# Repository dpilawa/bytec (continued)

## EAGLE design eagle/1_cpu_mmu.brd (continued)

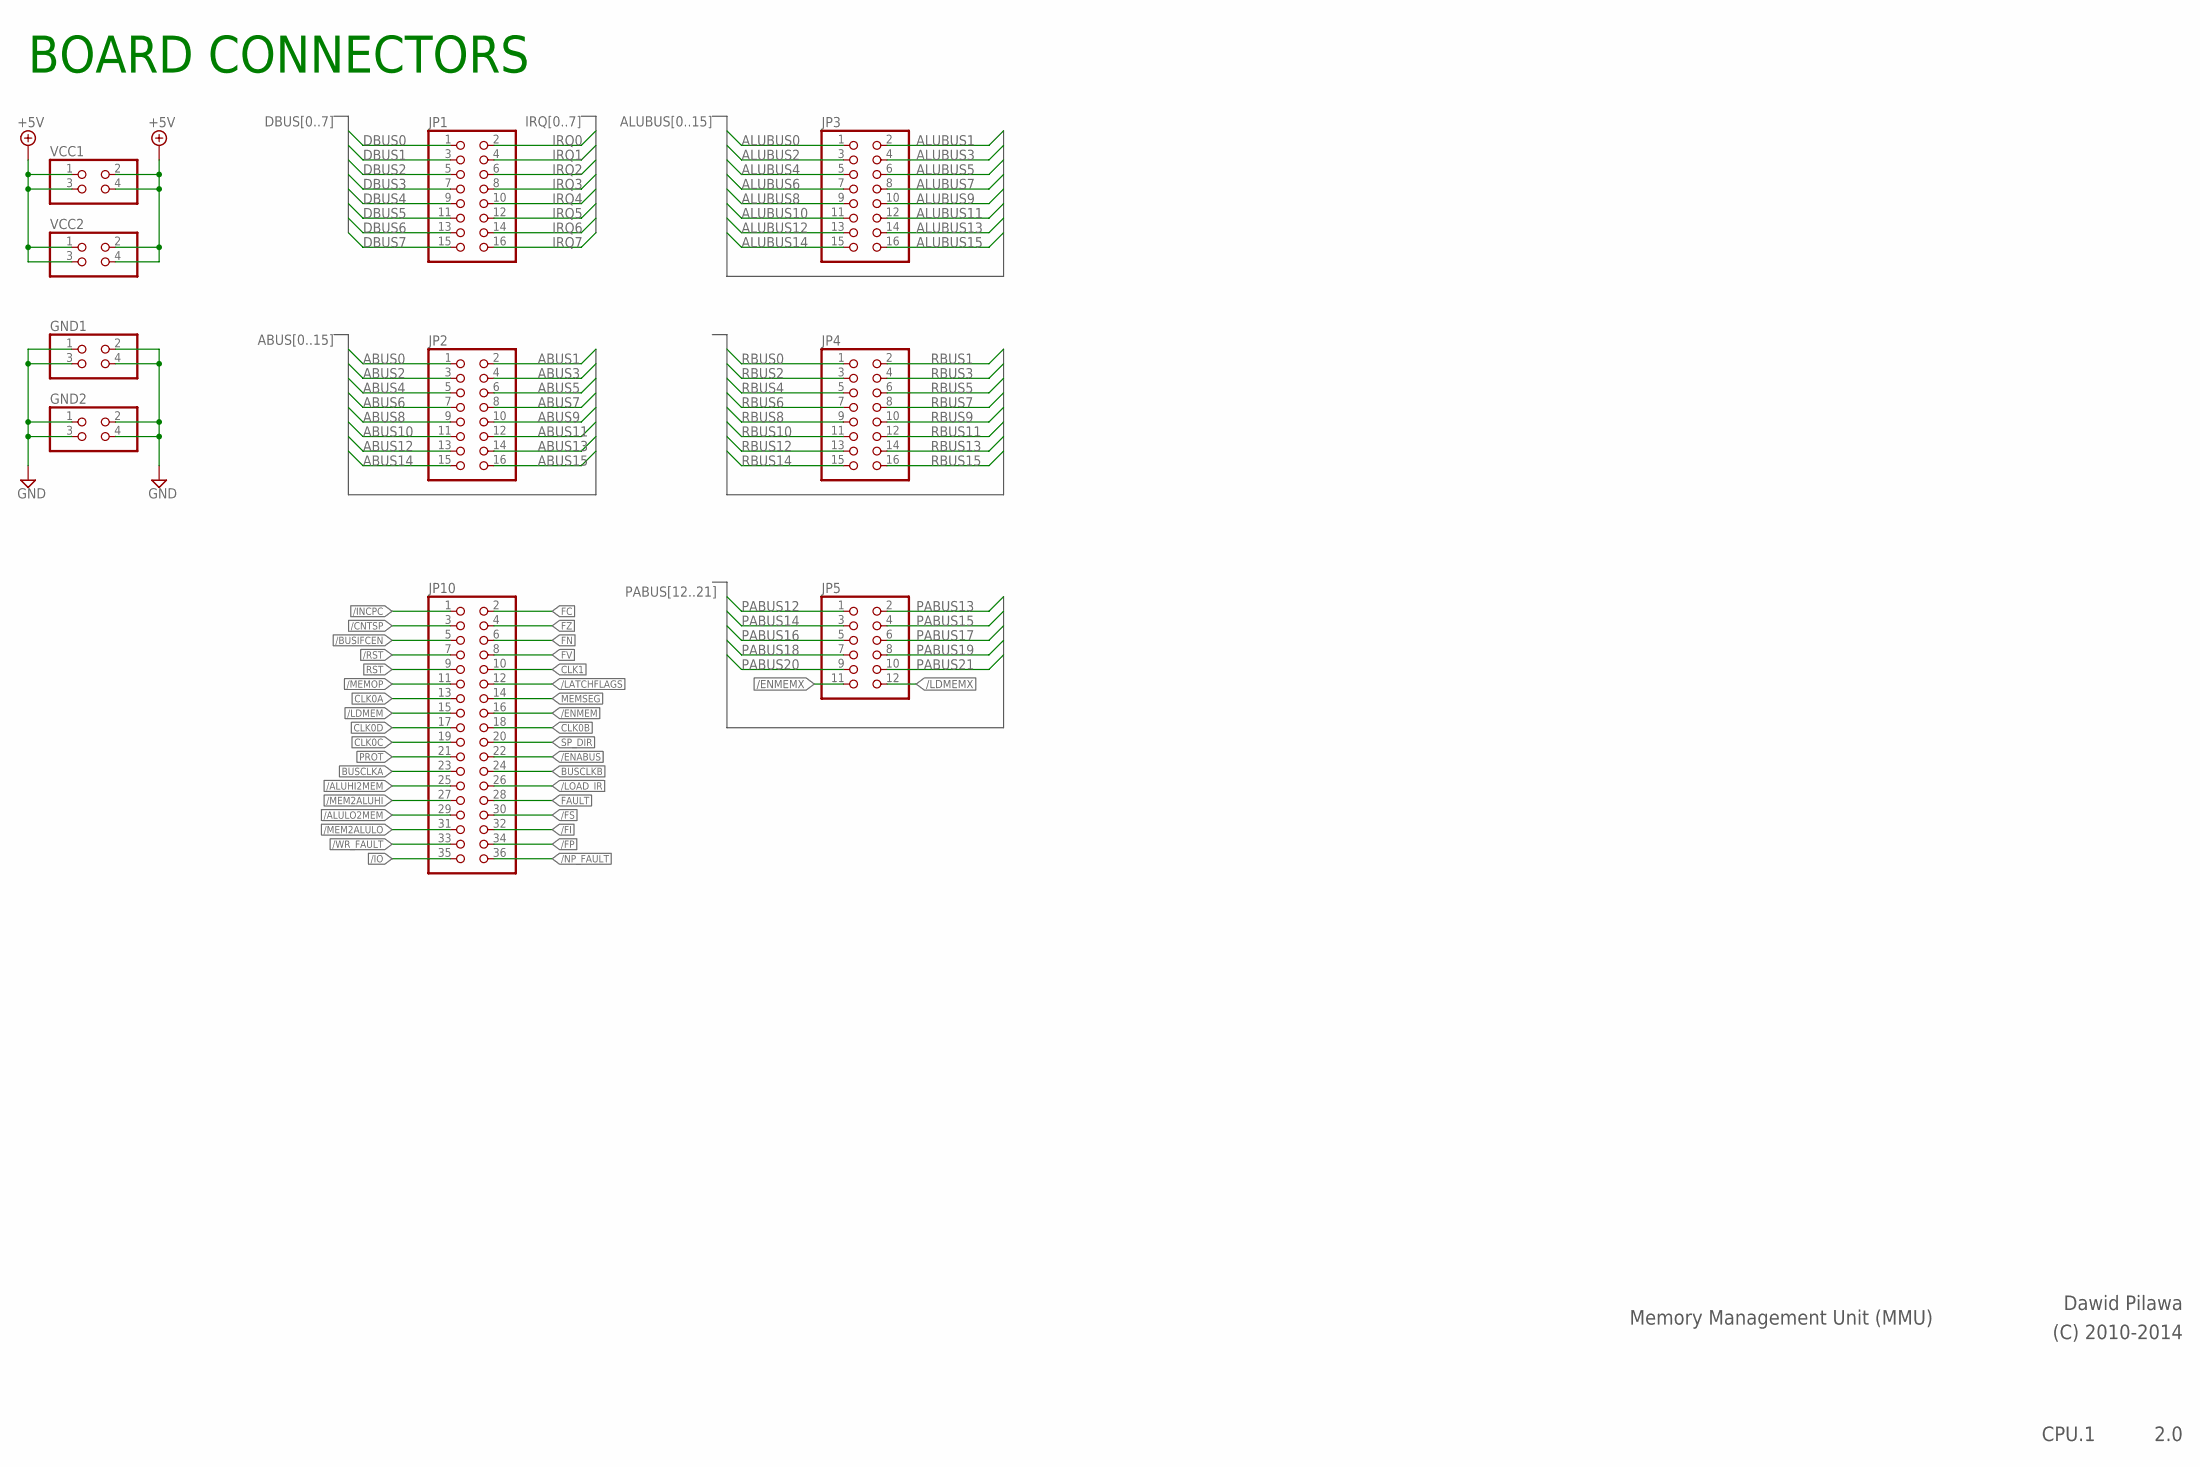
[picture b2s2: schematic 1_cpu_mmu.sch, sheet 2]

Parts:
GND1, GND2: PINHD-2X2; 2X02
JP1, JP2, JP3, JP4: PINHD-2X8; 2X08
JP5: PINHD-2X6; 2X06
JP10: PINHD-2X18; 2X18
VCC1, VCC2: PINHD-2X2; 2X02

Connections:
+5V: VCC1.1, VCC1.2, VCC1.3, VCC1.4, VCC2.1, VCC2.2, VCC2.3, VCC2.4; also elsewhere on the board
/ALUHI2MEM: JP10.25
/ALULO2MEM: JP10.29
/BUSIFCEN: JP10.5
/CNTSP: JP10.3
/ENABUS: JP10.22
/ENMEM: JP10.16; also elsewhere on the board
/ENMEMX: JP5.11; also elsewhere on the board
/FI: JP10.32
/FP: JP10.34; also elsewhere on the board
/FS: JP10.30; also elsewhere on the board
/INCPC: JP10.1
/IO: JP10.35; also elsewhere on the board
/LATCHFLAGS: JP10.12
/LDMEM: JP10.15; also elsewhere on the board
/LDMEMX: JP5.12; also elsewhere on the board
/LOAD_IR: JP10.26
/MEM2ALUHI: JP10.27
/MEM2ALULO: JP10.31
/MEMOP: JP10.11; also elsewhere on the board
/NP_FAULT: JP10.36; also elsewhere on the board
/RST: JP10.7
/WR_FAULT: JP10.33; also elsewhere on the board
ABUS0: JP2.1; also elsewhere on the board
ABUS1: JP2.2; also elsewhere on the board
ABUS2: JP2.3; also elsewhere on the board
ABUS3: JP2.4; also elsewhere on the board
ABUS4: JP2.5; also elsewhere on the board
ABUS5: JP2.6; also elsewhere on the board
ABUS6: JP2.7; also elsewhere on the board
ABUS7: JP2.8; also elsewhere on the board
ABUS8: JP2.9; also elsewhere on the board
ABUS9: JP2.10; also elsewhere on the board
ABUS10: JP2.11; also elsewhere on the board
ABUS11: JP2.12; also elsewhere on the board
ABUS12: JP2.13; also elsewhere on the board
ABUS13: JP2.14; also elsewhere on the board
ABUS14: JP2.15; also elsewhere on the board
ABUS15: JP2.16; also elsewhere on the board
ALUBUS0: JP3.1
ALUBUS1: JP3.2
ALUBUS2: JP3.3
ALUBUS3: JP3.4
ALUBUS4: JP3.5
ALUBUS5: JP3.6
ALUBUS6: JP3.7
ALUBUS7: JP3.8
ALUBUS8: JP3.9
ALUBUS9: JP3.10
ALUBUS10: JP3.11
ALUBUS11: JP3.12
ALUBUS12: JP3.13
ALUBUS13: JP3.14
ALUBUS14: JP3.15
ALUBUS15: JP3.16
BUSCLKA: JP10.23; also elsewhere on the board
BUSCLKB: JP10.24
CLK0A: JP10.13
CLK0B: JP10.18
CLK0C: JP10.19
CLK0D: JP10.17
CLK1: JP10.10
DBUS0: JP1.1; also elsewhere on the board
DBUS1: JP1.3; also elsewhere on the board
DBUS2: JP1.5; also elsewhere on the board
DBUS3: JP1.7; also elsewhere on the board
DBUS4: JP1.9; also elsewhere on the board
DBUS5: JP1.11; also elsewhere on the board
DBUS6: JP1.13; also elsewhere on the board
DBUS7: JP1.15; also elsewhere on the board
FAULT: JP10.28; also elsewhere on the board
FC: JP10.2
FN: JP10.6
FV: JP10.8
FZ: JP10.4
GND: GND1.1, GND1.2, GND1.3, GND1.4, GND2.1, GND2.2, GND2.3, GND2.4; also elsewhere on the board
IRQ0: JP1.2
IRQ1: JP1.4
IRQ2: JP1.6
IRQ3: JP1.8
IRQ4: JP1.10
IRQ5: JP1.12
IRQ6: JP1.14
IRQ7: JP1.16
MEMSEG: JP10.14; also elsewhere on the board
PABUS12: JP5.1; also elsewhere on the board
PABUS13: JP5.2; also elsewhere on the board
PABUS14: JP5.3; also elsewhere on the board
PABUS15: JP5.4; also elsewhere on the board
PABUS16: JP5.5; also elsewhere on the board
PABUS17: JP5.6; also elsewhere on the board
PABUS18: JP5.7; also elsewhere on the board
PABUS19: JP5.8; also elsewhere on the board
PABUS20: JP5.9; also elsewhere on the board
PABUS21: JP5.10; also elsewhere on the board
PROT: JP10.21
RBUS0: JP4.1
RBUS1: JP4.2
RBUS2: JP4.3
RBUS3: JP4.4
RBUS4: JP4.5
RBUS5: JP4.6
RBUS6: JP4.7
RBUS7: JP4.8
RBUS8: JP4.9
RBUS9: JP4.10
RBUS10: JP4.11
RBUS11: JP4.12
RBUS12: JP4.13
RBUS13: JP4.14
RBUS14: JP4.15
RBUS15: JP4.16
RST: JP10.9
SP_DIR: JP10.20

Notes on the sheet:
Memory Management Unit (MMU)
Dawid Pilawa
(C) 2010-2014
CPU.1
2.0
BOARD CONNECTORS

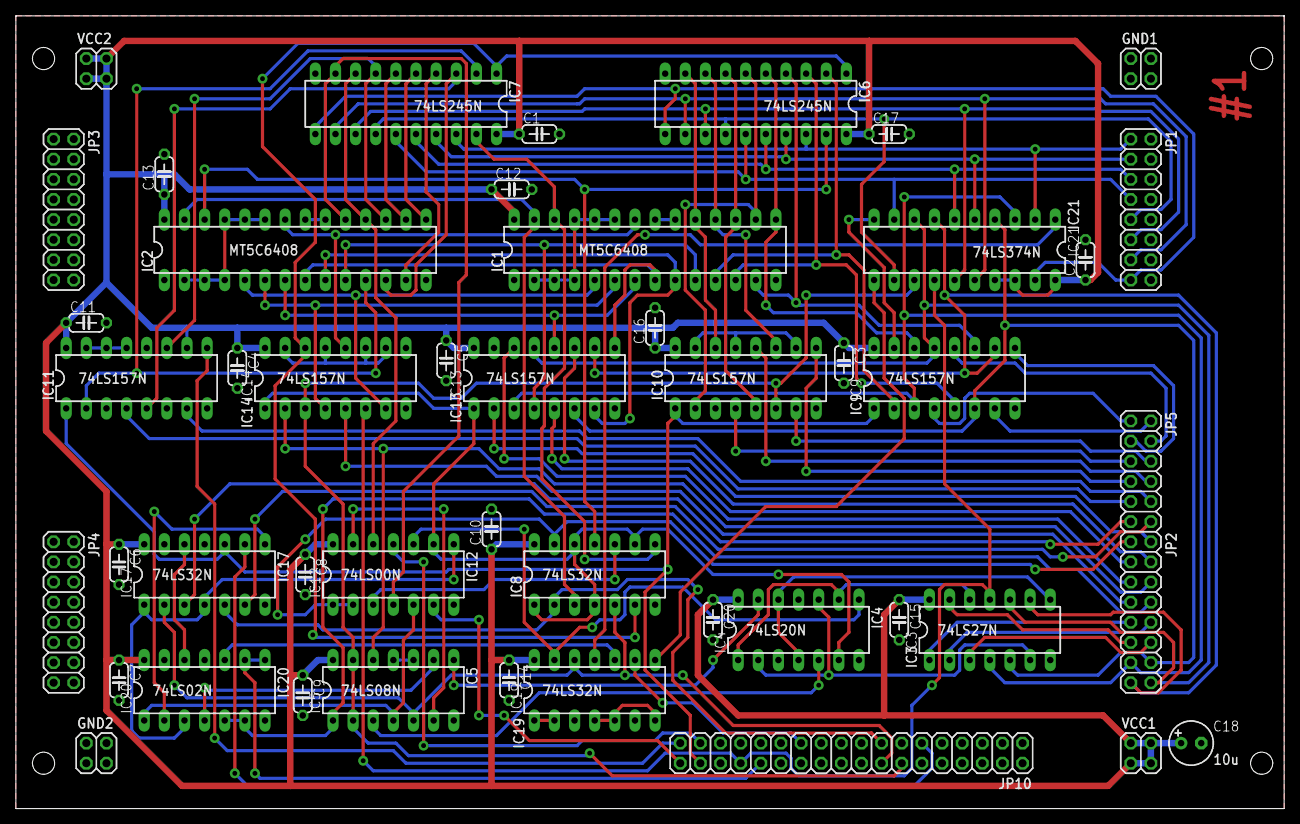
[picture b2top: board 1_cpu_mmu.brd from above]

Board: 2 copper layers, 160.0 x 100.0 mm, 47 parts (0 on the bottom side), 93 nets.

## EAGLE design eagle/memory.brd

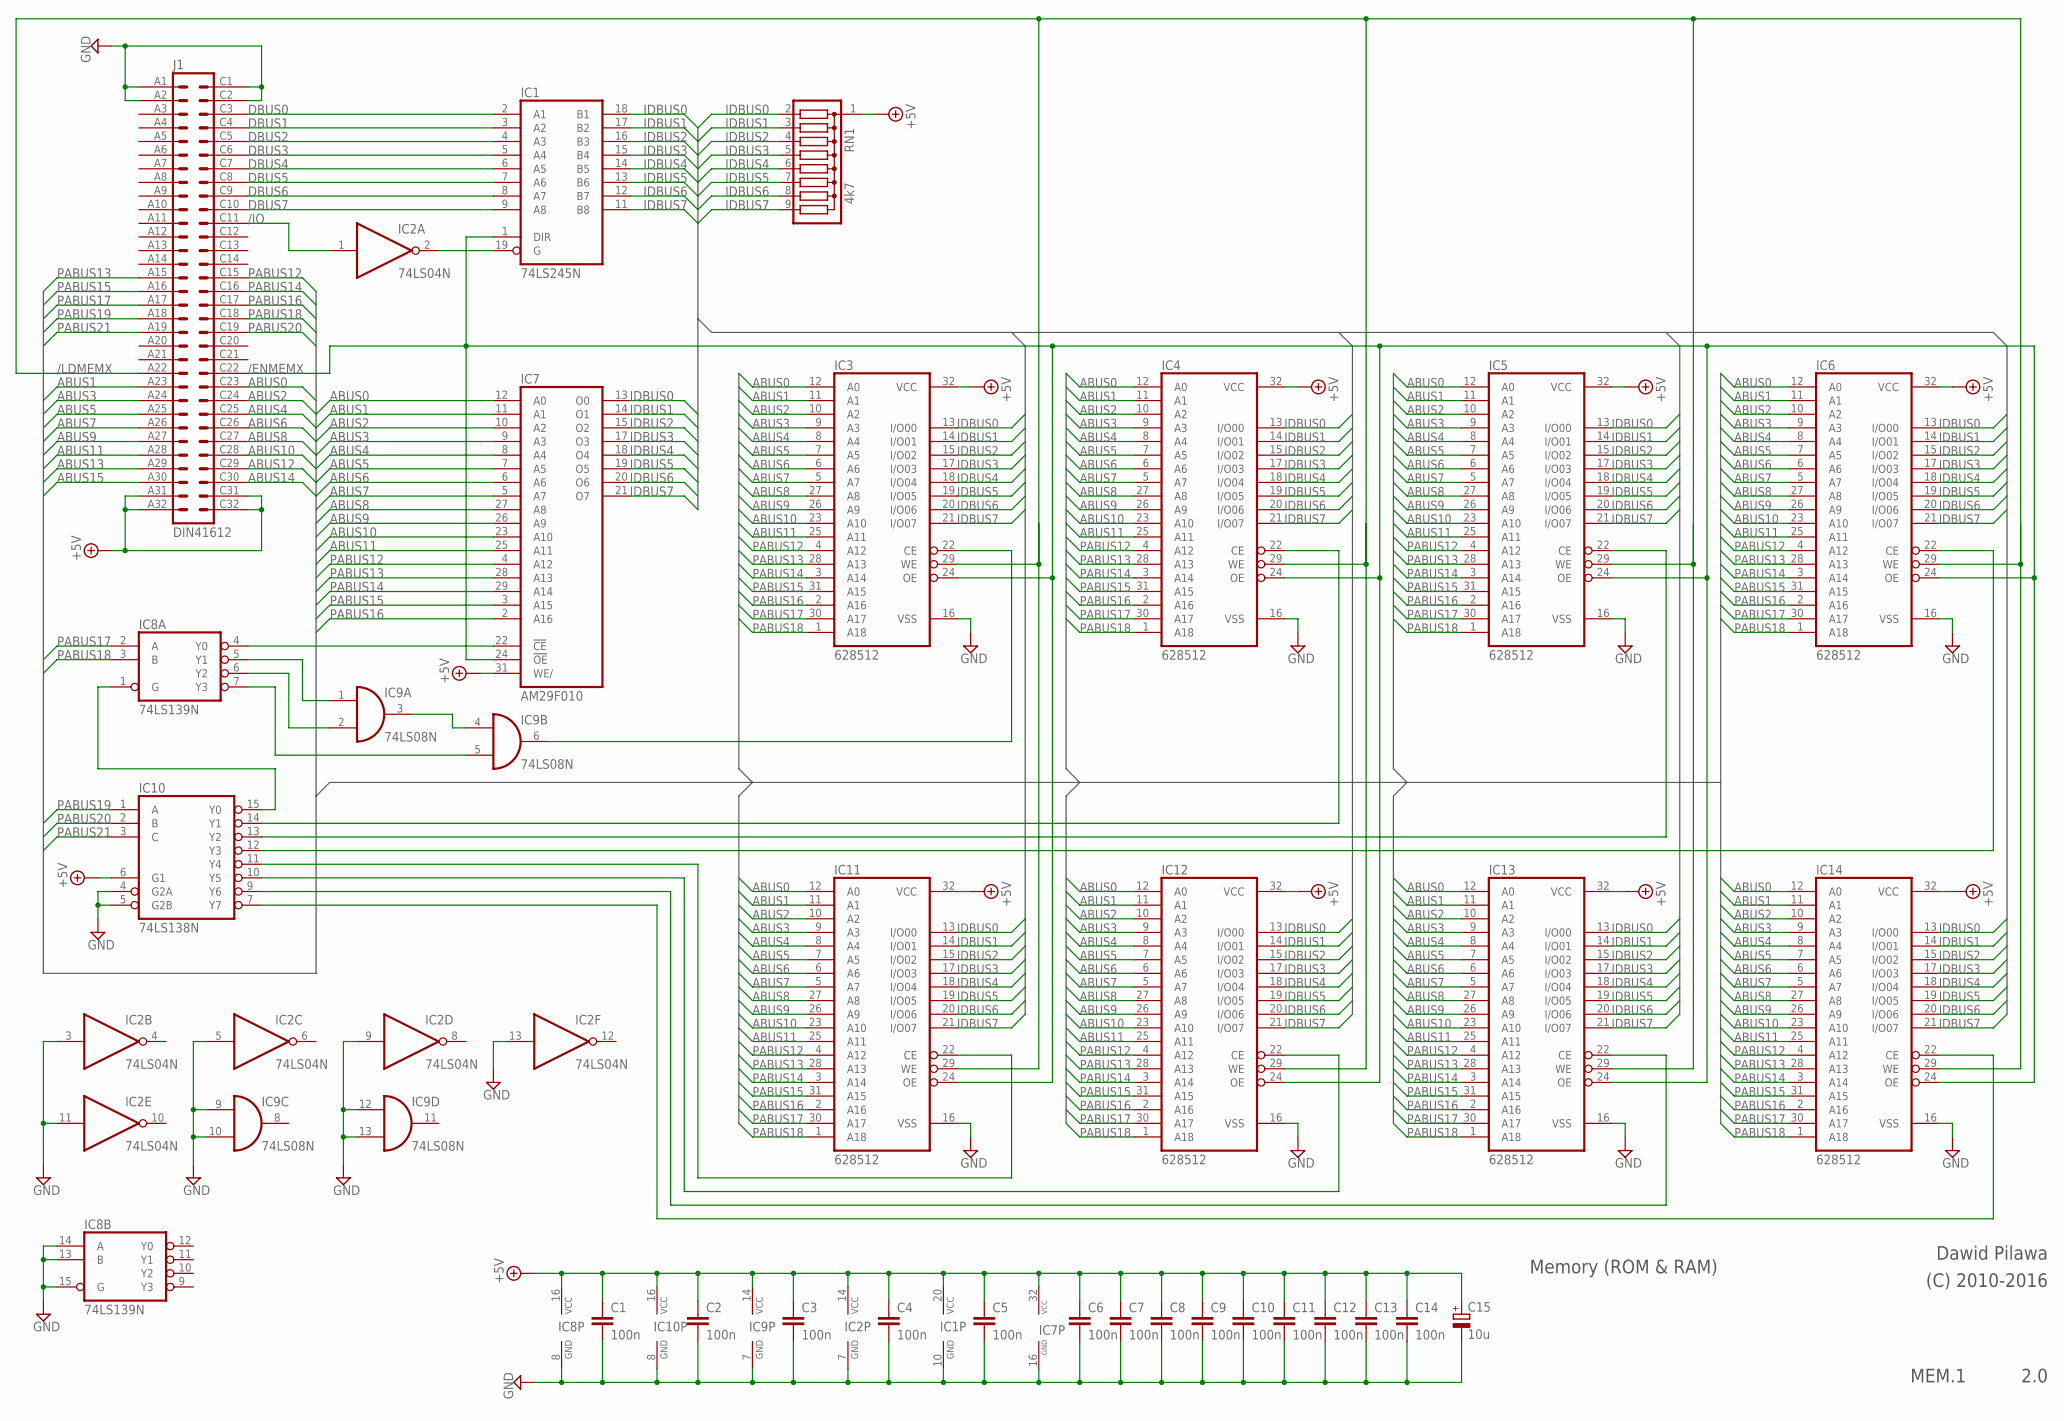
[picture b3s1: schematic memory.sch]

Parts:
C1, C2, C3, C4, C5, C6, C7, C8, C9, C10, C11, C12, C13, C14: 100n; C050-024X044
C15: 10u; E2,5-6
IC1: 74LS245N; DIL20
IC2: 74LS04N; DIL14
IC3, IC4, IC5, IC6, IC11, IC12, IC13, IC14: 628512; DIL32
IC7: AM29F010; DIL32-6
IC8: 74LS139N; DIL16
IC9: 74LS08N; DIL14
IC10: 74LS138N; DIL16
J1: DIN41612; VG64B
RN1: 4k7; SIL9

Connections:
+5V: C1.1, C2.1, C3.1, C4.1, C5.1, C6.1, C7.1, C8.1, C9.1, C10.1, C11.1, C12.1, C13.1, C14.1, C15.+, IC1.20 (VCC), IC2.14 (VCC), IC3.32 (VCC), IC4.32 (VCC), IC5.32 (VCC), IC6.32 (VCC), IC7.31 (WE/), IC7.32 (VCC), IC8.16 (VCC), IC9.14 (VCC), IC10.6 (G1), IC10.16 (VCC), IC11.32 (VCC), IC12.32 (VCC), IC13.32 (VCC), IC14.32 (VCC), J1.A31, J1.A32, J1.C31, J1.C32, RN1.1
/BANK0RAM: IC3.22 (CE), IC9.6 (O)
/BANK1: IC4.22 (CE), IC10.14 (Y1)
/BANK2: IC5.22 (CE), IC10.13 (Y2)
/BANK3: IC6.22 (CE), IC10.12 (Y3)
/BANK4: IC10.11 (Y4), IC11.22 (CE)
/BANK5: IC10.10 (Y5), IC12.22 (CE)
/BANK6: IC10.9 (Y6), IC13.22 (CE)
/BANK7: IC10.7 (Y7), IC14.22 (CE)
/ENMEMX: IC1.1 (DIR), IC3.24 (OE), IC4.24 (OE), IC5.24 (OE), IC6.24 (OE), IC7.24 (!OE), IC11.24 (OE), IC12.24 (OE), IC13.24 (OE), IC14.24 (OE), J1.C22
/IO: IC2.1 (I), J1.C11
/LDMEMX: IC3.29 (WE), IC4.29 (WE), IC5.29 (WE), IC6.29 (WE), IC11.29 (WE), IC12.29 (WE), IC13.29 (WE), IC14.29 (WE), J1.A22
ABUS0: IC3.12 (A0), IC4.12 (A0), IC5.12 (A0), IC6.12 (A0), IC7.12 (A0), IC11.12 (A0), IC12.12 (A0), IC13.12 (A0), IC14.12 (A0), J1.C23
ABUS1: IC3.11 (A1), IC4.11 (A1), IC5.11 (A1), IC6.11 (A1), IC7.11 (A1), IC11.11 (A1), IC12.11 (A1), IC13.11 (A1), IC14.11 (A1), J1.A23
ABUS2: IC3.10 (A2), IC4.10 (A2), IC5.10 (A2), IC6.10 (A2), IC7.10 (A2), IC11.10 (A2), IC12.10 (A2), IC13.10 (A2), IC14.10 (A2), J1.C24
ABUS3: IC3.9 (A3), IC4.9 (A3), IC5.9 (A3), IC6.9 (A3), IC7.9 (A3), IC11.9 (A3), IC12.9 (A3), IC13.9 (A3), IC14.9 (A3), J1.A24
ABUS4: IC3.8 (A4), IC4.8 (A4), IC5.8 (A4), IC6.8 (A4), IC7.8 (A4), IC11.8 (A4), IC12.8 (A4), IC13.8 (A4), IC14.8 (A4), J1.C25
ABUS5: IC3.7 (A5), IC4.7 (A5), IC5.7 (A5), IC6.7 (A5), IC7.7 (A5), IC11.7 (A5), IC12.7 (A5), IC13.7 (A5), IC14.7 (A5), J1.A25
ABUS6: IC3.6 (A6), IC4.6 (A6), IC5.6 (A6), IC6.6 (A6), IC7.6 (A6), IC11.6 (A6), IC12.6 (A6), IC13.6 (A6), IC14.6 (A6), J1.C26
ABUS7: IC3.5 (A7), IC4.5 (A7), IC5.5 (A7), IC6.5 (A7), IC7.5 (A7), IC11.5 (A7), IC12.5 (A7), IC13.5 (A7), IC14.5 (A7), J1.A26
ABUS8: IC3.27 (A8), IC4.27 (A8), IC5.27 (A8), IC6.27 (A8), IC7.27 (A8), IC11.27 (A8), IC12.27 (A8), IC13.27 (A8), IC14.27 (A8), J1.C27
ABUS9: IC3.26 (A9), IC4.26 (A9), IC5.26 (A9), IC6.26 (A9), IC7.26 (A9), IC11.26 (A9), IC12.26 (A9), IC13.26 (A9), IC14.26 (A9), J1.A27
ABUS10: IC3.23 (A10), IC4.23 (A10), IC5.23 (A10), IC6.23 (A10), IC7.23 (A10), IC11.23 (A10), IC12.23 (A10), IC13.23 (A10), IC14.23 (A10), J1.C28
ABUS11: IC3.25 (A11), IC4.25 (A11), IC5.25 (A11), IC6.25 (A11), IC7.25 (A11), IC11.25 (A11), IC12.25 (A11), IC13.25 (A11), IC14.25 (A11), J1.A28
ABUS12: J1.C29
ABUS13: J1.A29
ABUS14: J1.C30
ABUS15: J1.A30
DBUS0: IC1.2 (A1), J1.C3
DBUS1: IC1.3 (A2), J1.C4
DBUS2: IC1.4 (A3), J1.C5
DBUS3: IC1.5 (A4), J1.C6
DBUS4: IC1.6 (A5), J1.C7
DBUS5: IC1.7 (A6), J1.C8
DBUS6: IC1.8 (A7), J1.C9
DBUS7: IC1.9 (A8), J1.C10
GND: C1.2, C2.2, C3.2, C4.2, C5.2, C6.2, C7.2, C8.2, C9.2, C10.2, C11.2, C12.2, C13.2, C14.2, C15.-, IC1.10 (GND), IC2.3 (I), IC2.5 (I), IC2.7 (GND), IC2.9 (I), IC2.11 (I), IC2.13 (I), IC3.16 (VSS), IC4.16 (VSS), IC5.16 (VSS), IC6.16 (VSS), IC7.16 (GND), IC8.8 (GND), IC8.13 (B), IC8.14 (A), IC8.15 (G), IC9.7 (GND), IC9.9 (I0), IC9.10 (I1), IC9.12 (I0), IC9.13 (I1), IC10.4 (G2A), IC10.5 (G2B), IC10.8 (GND), IC11.16 (VSS), IC12.16 (VSS), IC13.16 (VSS), IC14.16 (VSS), J1.A1, J1.A2, J1.C1, J1.C2
IDBUS0: IC1.18 (B1), IC3.13 (I/O00), IC4.13 (I/O00), IC5.13 (I/O00), IC6.13 (I/O00), IC7.13 (O0), IC11.13 (I/O00), IC12.13 (I/O00), IC13.13 (I/O00), IC14.13 (I/O00), RN1.2
IDBUS1: IC1.17 (B2), IC3.14 (I/O01), IC4.14 (I/O01), IC5.14 (I/O01), IC6.14 (I/O01), IC7.14 (O1), IC11.14 (I/O01), IC12.14 (I/O01), IC13.14 (I/O01), IC14.14 (I/O01), RN1.3
IDBUS2: IC1.16 (B3), IC3.15 (I/O02), IC4.15 (I/O02), IC5.15 (I/O02), IC6.15 (I/O02), IC7.15 (O2), IC11.15 (I/O02), IC12.15 (I/O02), IC13.15 (I/O02), IC14.15 (I/O02), RN1.4
IDBUS3: IC1.15 (B4), IC3.17 (I/O03), IC4.17 (I/O03), IC5.17 (I/O03), IC6.17 (I/O03), IC7.17 (O3), IC11.17 (I/O03), IC12.17 (I/O03), IC13.17 (I/O03), IC14.17 (I/O03), RN1.5
IDBUS4: IC1.14 (B5), IC3.18 (I/O04), IC4.18 (I/O04), IC5.18 (I/O04), IC6.18 (I/O04), IC7.18 (O4), IC11.18 (I/O04), IC12.18 (I/O04), IC13.18 (I/O04), IC14.18 (I/O04), RN1.6
IDBUS5: IC1.13 (B6), IC3.19 (I/O05), IC4.19 (I/O05), IC5.19 (I/O05), IC6.19 (I/O05), IC7.19 (O5), IC11.19 (I/O05), IC12.19 (I/O05), IC13.19 (I/O05), IC14.19 (I/O05), RN1.7
IDBUS6: IC1.12 (B7), IC3.20 (I/O06), IC4.20 (I/O06), IC5.20 (I/O06), IC6.20 (I/O06), IC7.20 (O6), IC11.20 (I/O06), IC12.20 (I/O06), IC13.20 (I/O06), IC14.20 (I/O06), RN1.8
IDBUS7: IC1.11 (B8), IC3.21 (I/O07), IC4.21 (I/O07), IC5.21 (I/O07), IC6.21 (I/O07), IC7.21 (O7), IC11.21 (I/O07), IC12.21 (I/O07), IC13.21 (I/O07), IC14.21 (I/O07), RN1.9
unnamed: IC1.19 (G), IC2.2 (O)
unnamed: IC8.1 (G), IC10.15 (Y0)
unnamed: IC8.5 (Y1), IC9.1 (I0)
unnamed: IC8.6 (Y2), IC9.2 (I1)
unnamed: IC7.22 (!CE), IC8.4 (Y0)
unnamed: IC8.7 (Y3), IC9.5 (I1)
unnamed: IC9.3 (O), IC9.4 (I0)
PABUS12: IC3.4 (A12), IC4.4 (A12), IC5.4 (A12), IC6.4 (A12), IC7.4 (A12), IC11.4 (A12), IC12.4 (A12), IC13.4 (A12), IC14.4 (A12), J1.C15
PABUS13: IC3.28 (A13), IC4.28 (A13), IC5.28 (A13), IC6.28 (A13), IC7.28 (A13), IC11.28 (A13), IC12.28 (A13), IC13.28 (A13), IC14.28 (A13), J1.A15
PABUS14: IC3.3 (A14), IC4.3 (A14), IC5.3 (A14), IC6.3 (A14), IC7.29 (A14), IC11.3 (A14), IC12.3 (A14), IC13.3 (A14), IC14.3 (A14), J1.C16
PABUS15: IC3.31 (A15), IC4.31 (A15), IC5.31 (A15), IC6.31 (A15), IC7.3 (A15), IC11.31 (A15), IC12.31 (A15), IC13.31 (A15), IC14.31 (A15), J1.A16
PABUS16: IC3.2 (A16), IC4.2 (A16), IC5.2 (A16), IC6.2 (A16), IC7.2 (A16), IC11.2 (A16), IC12.2 (A16), IC13.2 (A16), IC14.2 (A16), J1.C17
PABUS17: IC3.30 (A17), IC4.30 (A17), IC5.30 (A17), IC6.30 (A17), IC8.2 (A), IC11.30 (A17), IC12.30 (A17), IC13.30 (A17), IC14.30 (A17), J1.A17
PABUS18: IC3.1 (A18), IC4.1 (A18), IC5.1 (A18), IC6.1 (A18), IC8.3 (B), IC11.1 (A18), IC12.1 (A18), IC13.1 (A18), IC14.1 (A18), J1.C18
PABUS19: IC10.1 (A), J1.A18
PABUS20: IC10.2 (B), J1.C19
PABUS21: IC10.3 (C), J1.A19

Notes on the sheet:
Memory (ROM & RAM)
Dawid Pilawa
(C) 2010-2016
MEM.1
2.0

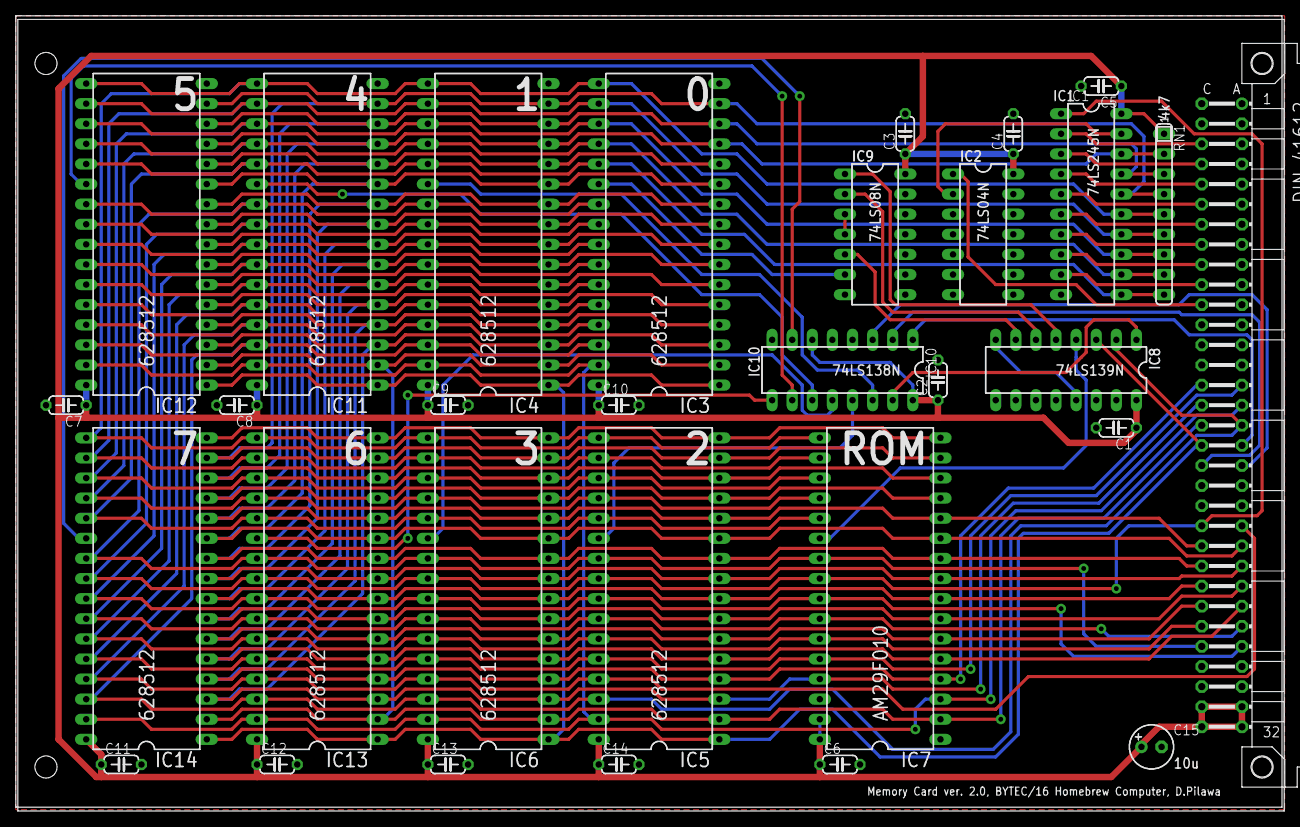
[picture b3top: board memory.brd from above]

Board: 2 copper layers, 160.0 x 100.0 mm, 31 parts (0 on the bottom side), 58 nets.

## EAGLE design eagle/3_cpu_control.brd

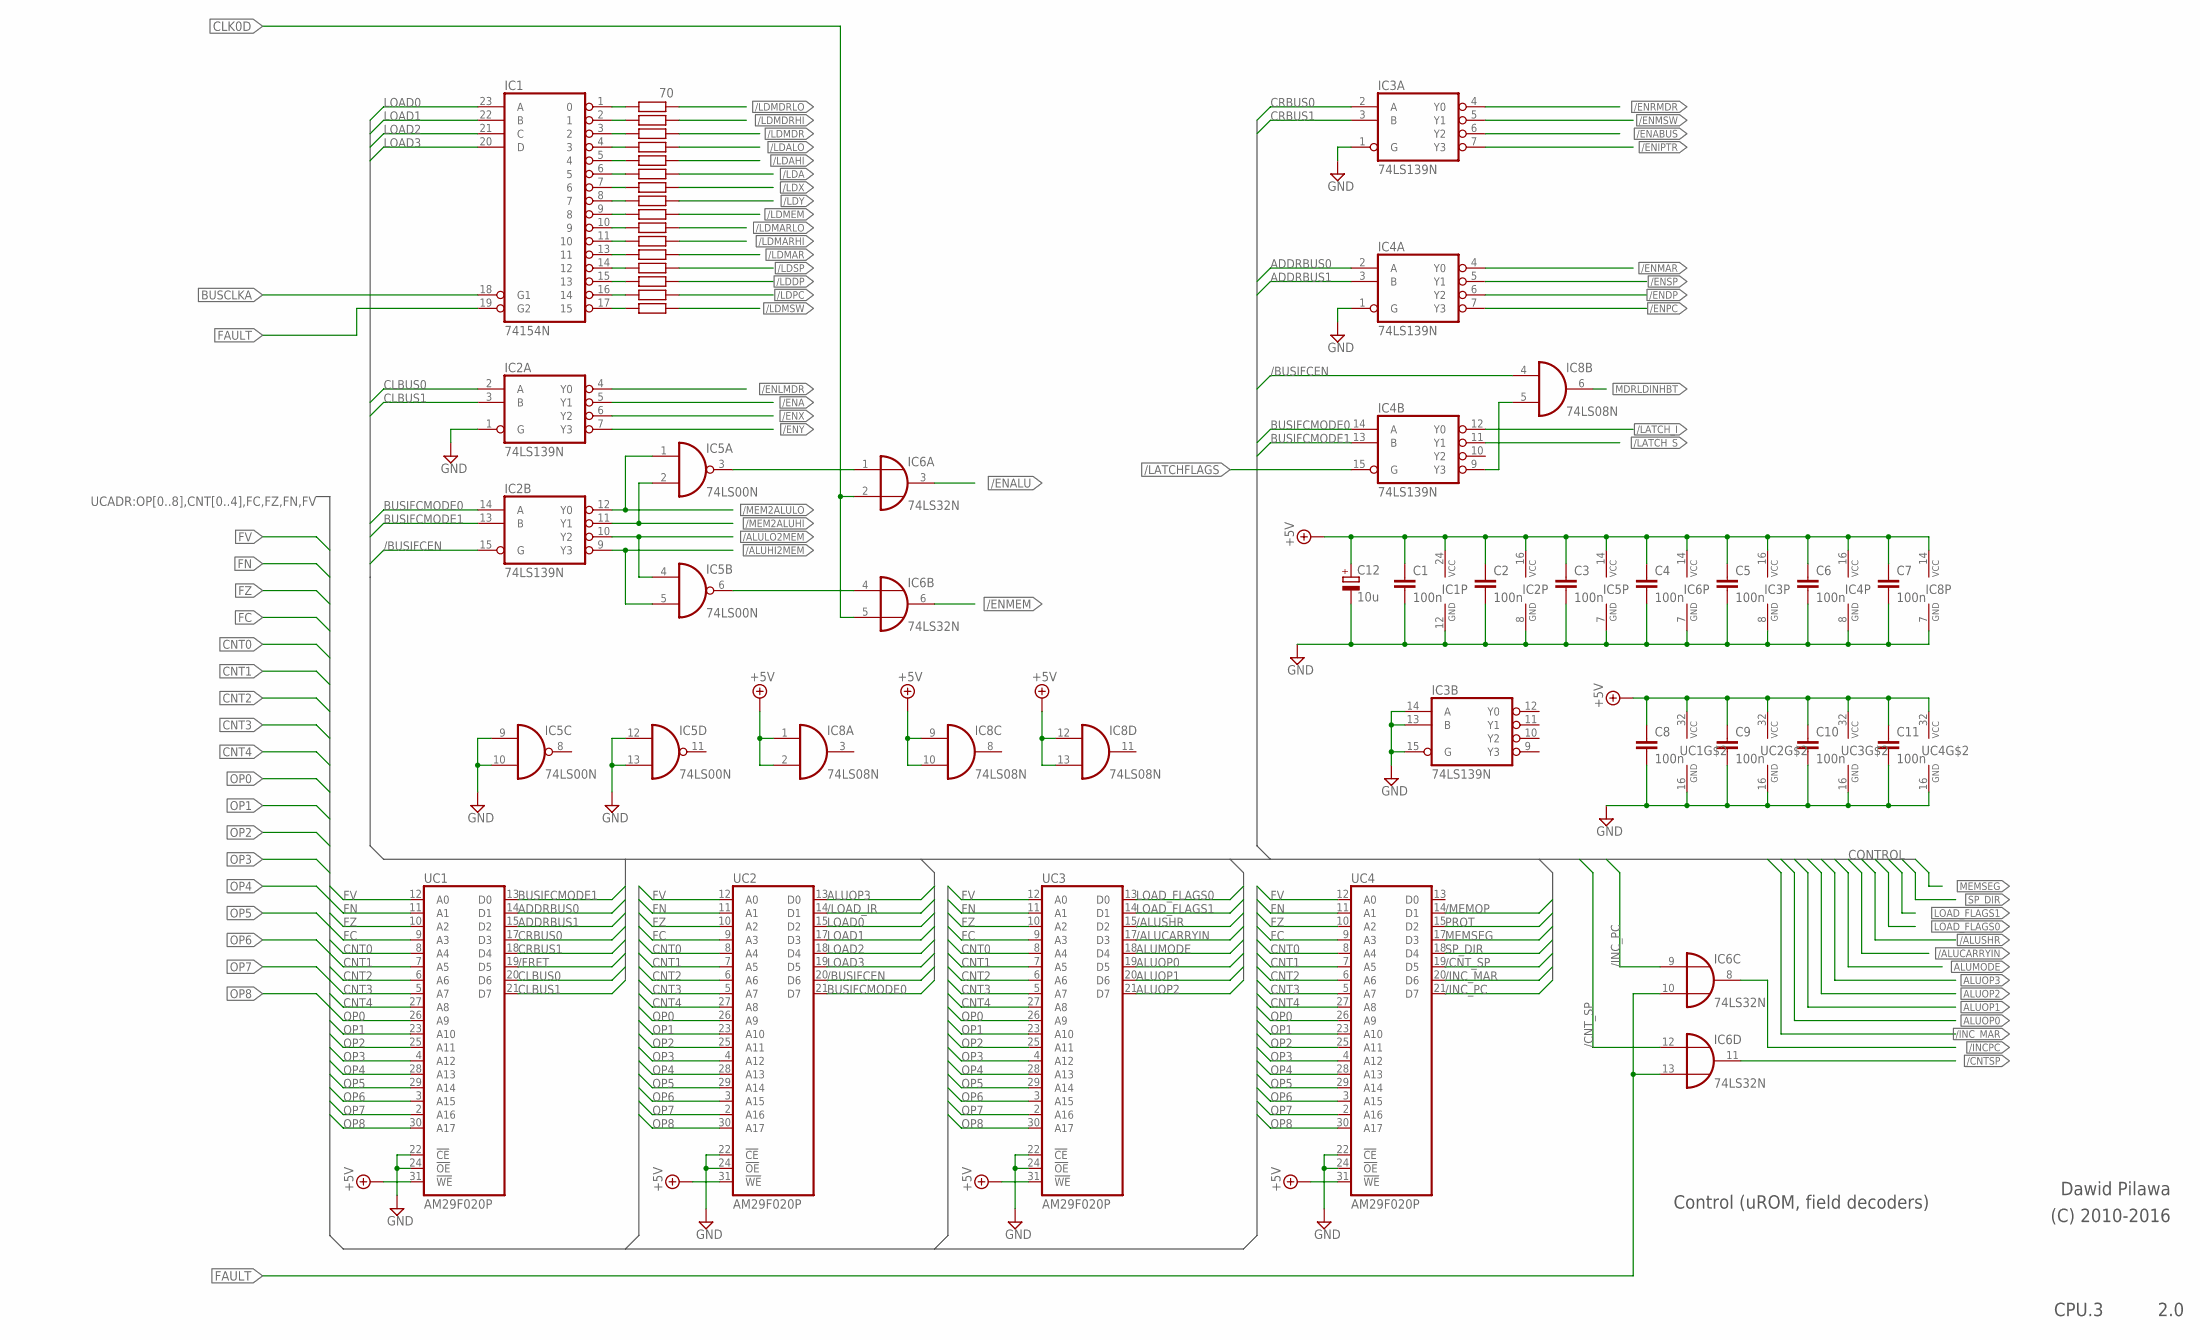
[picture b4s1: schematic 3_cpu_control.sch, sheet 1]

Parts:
C1, C2, C3, C4, C5, C6, C7, C8, C9, C10, C11: 100n; C050-024X044
C12: 10u; E5-6
IC1: 74154N; DIL24-6
IC2, IC3, IC4: 74LS139N; DIL16
IC5: 74LS00N; DIL14
IC6: 74LS32N; DIL14
IC8: 74LS08N; DIL14
R1: 70; 0204/7
R2, R3, R4, R5, R6, R7, R8, R9, R10, R11, R12, R13, R14, R15, R16: R-EU_0204/7; 0204/7
UC1, UC2, UC3, UC4: AM29F020P; DIL32-6

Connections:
+5V: C1.1, C2.1, C3.1, C4.1, C5.1, C6.1, C7.1, C8.1, C9.1, C10.1, C11.1, C12.+, IC1.24 (VCC), IC2.16 (VCC), IC3.16 (VCC), IC4.16 (VCC), IC5.14 (VCC), IC6.14 (VCC), IC8.1 (I0), IC8.2 (I1), IC8.9 (I0), IC8.10 (I1), IC8.12 (I0), IC8.13 (I1), IC8.14 (VCC), UC1.31 (!WE), UC1.32 (AVCC), UC2.31 (!WE), UC2.32 (AVCC), UC3.31 (!WE), UC3.32 (AVCC), UC4.31 (!WE), UC4.32 (AVCC); also elsewhere on the board
/ALUCARRYIN: UC3.17 (D3); also elsewhere on the board
/ALUHI2MEM: IC2.9 (Y3), IC5.5 (I1); also elsewhere on the board
/ALULO2MEM: IC2.10 (Y2), IC5.4 (I0); also elsewhere on the board
/ALUSHR: UC3.15 (D2); also elsewhere on the board
/BUSIFCEN: IC2.15 (G), IC8.4 (I0), UC2.20 (D6); also elsewhere on the board
/CNTSP: IC6.11 (O); also elsewhere on the board
/CNT_SP: IC6.12 (I0), UC4.19 (D5)
/ENA: IC2.5 (Y1); also elsewhere on the board
/ENABUS: IC3.6 (Y2); also elsewhere on the board
/ENALU: IC6.3 (O); also elsewhere on the board
/ENDP: IC4.6 (Y2); also elsewhere on the board
/ENIPTR: IC3.7 (Y3); also elsewhere on the board
/ENLMDR: IC2.4 (Y0); also elsewhere on the board
/ENMAR: IC4.4 (Y0); also elsewhere on the board
/ENMEM: IC6.6 (O); also elsewhere on the board
/ENMSW: IC3.5 (Y1); also elsewhere on the board
/ENPC: IC4.7 (Y3); also elsewhere on the board
/ENRMDR: IC3.4 (Y0); also elsewhere on the board
/ENSP: IC4.5 (Y1); also elsewhere on the board
/ENX: IC2.6 (Y2); also elsewhere on the board
/ENY: IC2.7 (Y3); also elsewhere on the board
/FRET: UC1.19 (D5); also elsewhere on the board
/INCPC: IC6.8 (O); also elsewhere on the board
/INC_MAR: UC4.20 (D6); also elsewhere on the board
/INC_PC: IC6.9 (I0), UC4.21 (D7)
/LATCHFLAGS: IC4.15 (G); also elsewhere on the board
/LATCH_I: IC4.12 (Y0); also elsewhere on the board
/LATCH_NONE: IC4.9 (Y3), IC8.5 (I1)
/LATCH_S: IC4.11 (Y1); also elsewhere on the board
/LDA: R6.2; also elsewhere on the board
/LDAHI: R5.2; also elsewhere on the board
/LDALO: R4.2; also elsewhere on the board
/LDDP: R14.2; also elsewhere on the board
/LDMAR: R12.2; also elsewhere on the board
/LDMARHI: R11.2; also elsewhere on the board
/LDMARLO: R10.2; also elsewhere on the board
/LDMDR: R3.2; also elsewhere on the board
/LDMDRHI: R2.2; also elsewhere on the board
/LDMDRLO: R1.2; also elsewhere on the board
/LDMEM: R9.2; also elsewhere on the board
/LDMSW: R16.2; also elsewhere on the board
/LDPC: R15.2; also elsewhere on the board
/LDSP: R13.2; also elsewhere on the board
/LDX: R7.2; also elsewhere on the board
/LDY: R8.2; also elsewhere on the board
/LOAD_IR: UC2.14 (D1); also elsewhere on the board
/MEM2ALUHI: IC2.11 (Y1), IC5.2 (I1); also elsewhere on the board
/MEM2ALULO: IC2.12 (Y0), IC5.1 (I0); also elsewhere on the board
/MEMOP: UC4.14 (D1); also elsewhere on the board
ADDRBUS0: IC4.2 (A), UC1.14 (D1)
ADDRBUS1: IC4.3 (B), UC1.15 (D2)
ALUMODE: UC3.18 (D4); also elsewhere on the board
ALUOP0: UC3.19 (D5); also elsewhere on the board
ALUOP1: UC3.20 (D6); also elsewhere on the board
ALUOP2: UC3.21 (D7); also elsewhere on the board
ALUOP3: UC2.13 (D0); also elsewhere on the board
BUSCLKA: IC1.18 (G1); also elsewhere on the board
BUSIFCMODE0: IC2.14 (A), IC4.14 (A), UC2.21 (D7)
BUSIFCMODE1: IC2.13 (B), IC4.13 (B), UC1.13 (D0)
CLBUS0: IC2.2 (A), UC1.20 (D6)
CLBUS1: IC2.3 (B), UC1.21 (D7)
CLK0D: IC6.2 (I1), IC6.5 (I1); also elsewhere on the board
CNT0: UC1.8 (A4), UC2.8 (A4), UC3.8 (A4), UC4.8 (A4); also elsewhere on the board
CNT1: UC1.7 (A5), UC2.7 (A5), UC3.7 (A5), UC4.7 (A5); also elsewhere on the board
CNT2: UC1.6 (A6), UC2.6 (A6), UC3.6 (A6), UC4.6 (A6); also elsewhere on the board
CNT3: UC1.5 (A7), UC2.5 (A7), UC3.5 (A7), UC4.5 (A7); also elsewhere on the board
CNT4: UC1.27 (A8), UC2.27 (A8), UC3.27 (A8), UC4.27 (A8); also elsewhere on the board
CRBUS0: IC3.2 (A), UC1.17 (D3)
CRBUS1: IC3.3 (B), UC1.18 (D4)
FAULT: IC1.19 (G2), IC6.10 (I1), IC6.13 (I1); also elsewhere on the board
FC: UC1.9 (A3), UC2.9 (A3), UC3.9 (A3), UC4.9 (A3); also elsewhere on the board
FN: UC1.11 (A1), UC2.11 (A1), UC3.11 (A1), UC4.11 (A1); also elsewhere on the board
FV: UC1.12 (A0), UC2.12 (A0), UC3.12 (A0), UC4.12 (A0); also elsewhere on the board
FZ: UC1.10 (A2), UC2.10 (A2), UC3.10 (A2), UC4.10 (A2); also elsewhere on the board
GND: C1.2, C2.2, C3.2, C4.2, C5.2, C6.2, C7.2, C8.2, C9.2, C10.2, C11.2, C12.-, IC1.12 (GND), IC2.1 (G), IC2.8 (GND), IC3.1 (G), IC3.8 (GND), IC3.13 (B), IC3.14 (A), IC3.15 (G), IC4.1 (G), IC4.8 (GND), IC5.7 (GND), IC5.9 (I0), IC5.10 (I1), IC5.12 (I0), IC5.13 (I1), IC6.7 (GND), IC8.7 (GND), UC1.16 (AGND), UC1.22 (!CE), UC1.24 (!OE), UC2.16 (AGND), UC2.22 (!CE), UC2.24 (!OE), UC3.16 (AGND), UC3.22 (!CE), UC3.24 (!OE), UC4.16 (AGND), UC4.22 (!CE), UC4.24 (!OE); also elsewhere on the board
LOAD0: IC1.23 (A), UC2.15 (D2)
LOAD1: IC1.22 (B), UC2.17 (D3)
LOAD2: IC1.21 (C), UC2.18 (D4)
LOAD3: IC1.20 (D), UC2.19 (D5)
LOAD_FLAGS0: UC3.13 (D0); also elsewhere on the board
LOAD_FLAGS1: UC3.14 (D1); also elsewhere on the board
MDRLDINHBT: IC8.6 (O); also elsewhere on the board
MEMSEG: UC4.17 (D3); also elsewhere on the board
unnamed: IC1.16 (14), R15.1
unnamed: IC5.3 (O), IC6.1 (I0)
unnamed: IC5.6 (O), IC6.4 (I0)
unnamed: IC1.1 (0), R1.1
unnamed: IC1.2 (1), R2.1
unnamed: IC1.3 (2), R3.1
unnamed: IC1.4 (3), R4.1
unnamed: IC1.5 (4), R5.1
unnamed: IC1.6 (5), R6.1
unnamed: IC1.7 (6), R7.1
unnamed: IC1.8 (7), R8.1
unnamed: IC1.9 (8), R9.1
unnamed: IC1.10 (9), R10.1
unnamed: IC1.11 (10), R11.1
unnamed: IC1.13 (11), R12.1
unnamed: IC1.14 (12), R13.1
unnamed: IC1.15 (13), R14.1
unnamed: IC1.17 (15), R16.1
OP0: UC1.26 (A9), UC2.26 (A9), UC3.26 (A9), UC4.26 (A9); also elsewhere on the board
OP1: UC1.23 (A10), UC2.23 (A10), UC3.23 (A10), UC4.23 (A10); also elsewhere on the board
OP2: UC1.25 (A11), UC2.25 (A11), UC3.25 (A11), UC4.25 (A11); also elsewhere on the board
OP3: UC1.4 (A12), UC2.4 (A12), UC3.4 (A12), UC4.4 (A12); also elsewhere on the board
OP4: UC1.28 (A13), UC2.28 (A13), UC3.28 (A13), UC4.28 (A13); also elsewhere on the board
OP5: UC1.29 (A14), UC2.29 (A14), UC3.29 (A14), UC4.29 (A14); also elsewhere on the board
OP6: UC1.3 (A15), UC2.3 (A15), UC3.3 (A15), UC4.3 (A15); also elsewhere on the board
OP7: UC1.2 (A16), UC2.2 (A16), UC3.2 (A16), UC4.2 (A16); also elsewhere on the board
OP8: UC1.30 (A17), UC2.30 (A17), UC3.30 (A17), UC4.30 (A17); also elsewhere on the board
PROT: UC4.15 (D2); also elsewhere on the board
SP_DIR: UC4.18 (D4); also elsewhere on the board

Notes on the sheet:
Control (uROM, field decoders)
2.0
Dawid Pilawa
(C) 2010-2016
CPU.3
CONTROL
